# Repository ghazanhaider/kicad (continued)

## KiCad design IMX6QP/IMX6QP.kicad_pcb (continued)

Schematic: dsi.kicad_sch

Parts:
U1: MCIMX6QP5EYM; BGA-624_21x21mm_Layout25x25_P0.8mm

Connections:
CSI_D1M: U1.D1 (CSI_D1M); also elsewhere on the board
CSI_D1P: U1.D2 (CSI_D1P); also elsewhere on the board
CSI_D3P: U1.F1 (CSI_D3P); also elsewhere on the board
HDMI_VPH: U1.K7 (NVCC_MIPI); also elsewhere on the board

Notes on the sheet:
MIPI Display Check standards
MIPI camera RPI uses 15-pin 1mm connector (SFW15R-2STE1LF) with this pinout: 1 GND 2 D0_N 3 D0_P 4 GND 5 D1_N 6 D1_P 7 GND 8 CK_N 9 CK_P 10 GND 11 IO0 - Power enable 12 IO1 - LED indicator 13 SCL 14 SDA 15 3V3 This connector looks like 16-bit parallel/RGB input

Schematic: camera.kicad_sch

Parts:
U1: MCIMX6QP5EYM; BGA-624_21x21mm_Layout25x25_P0.8mm

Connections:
3V3_SW2: U1.N7 (NVCC_CSI); also elsewhere on the board
CSI0_DAT5: U1.P2 (CSI0_DAT5); also elsewhere on the board
CSI0_DATA_EN: U1.P3 (CSI0_DATA_EN); also elsewhere on the board
CSI0_MCLK: U1.P4 (CSI0_MCLK); also elsewhere on the board
CSI0_PIXCLK: U1.P1 (CSI0_PIXCLK); also elsewhere on the board
I2C1_SCL: U1.N5 (CSI0_DAT9); also elsewhere on the board
I2C1_SDA: U1.N6 (CSI0_DAT8); also elsewhere on the board
UART1_RX_DATA: U1.M3 (CSI0_DAT11); also elsewhere on the board
UART1_TX_DATA: U1.M1 (CSI0_DAT10); also elsewhere on the board

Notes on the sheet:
Do not use

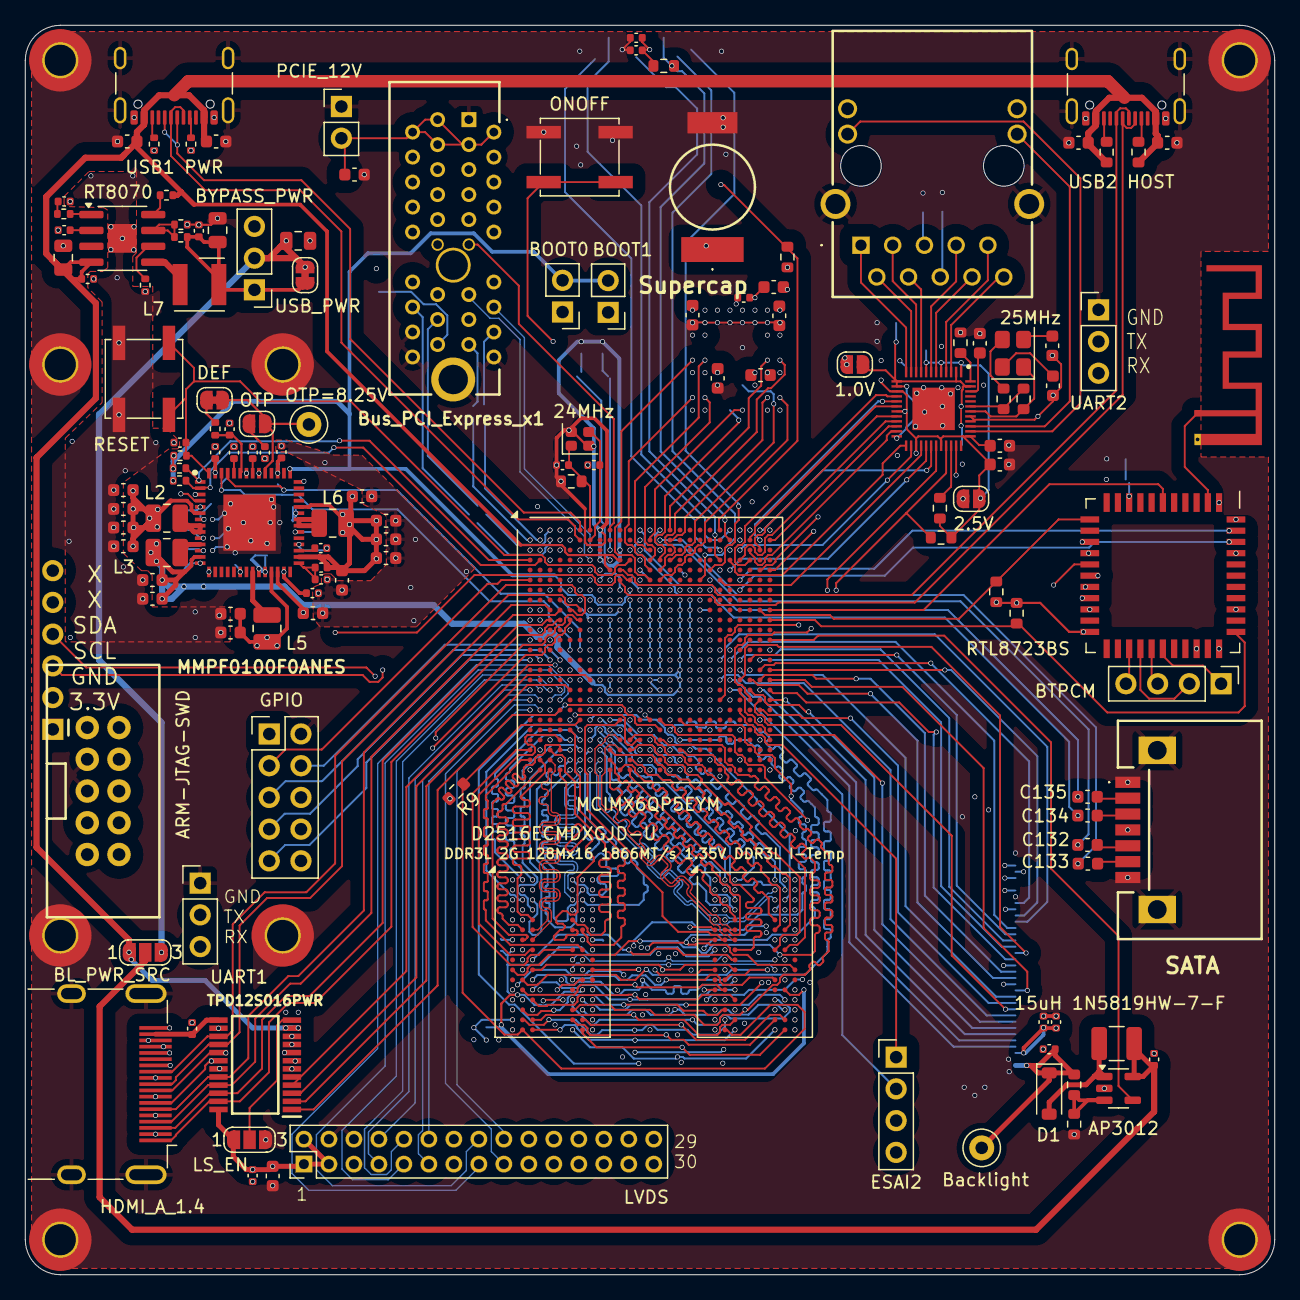
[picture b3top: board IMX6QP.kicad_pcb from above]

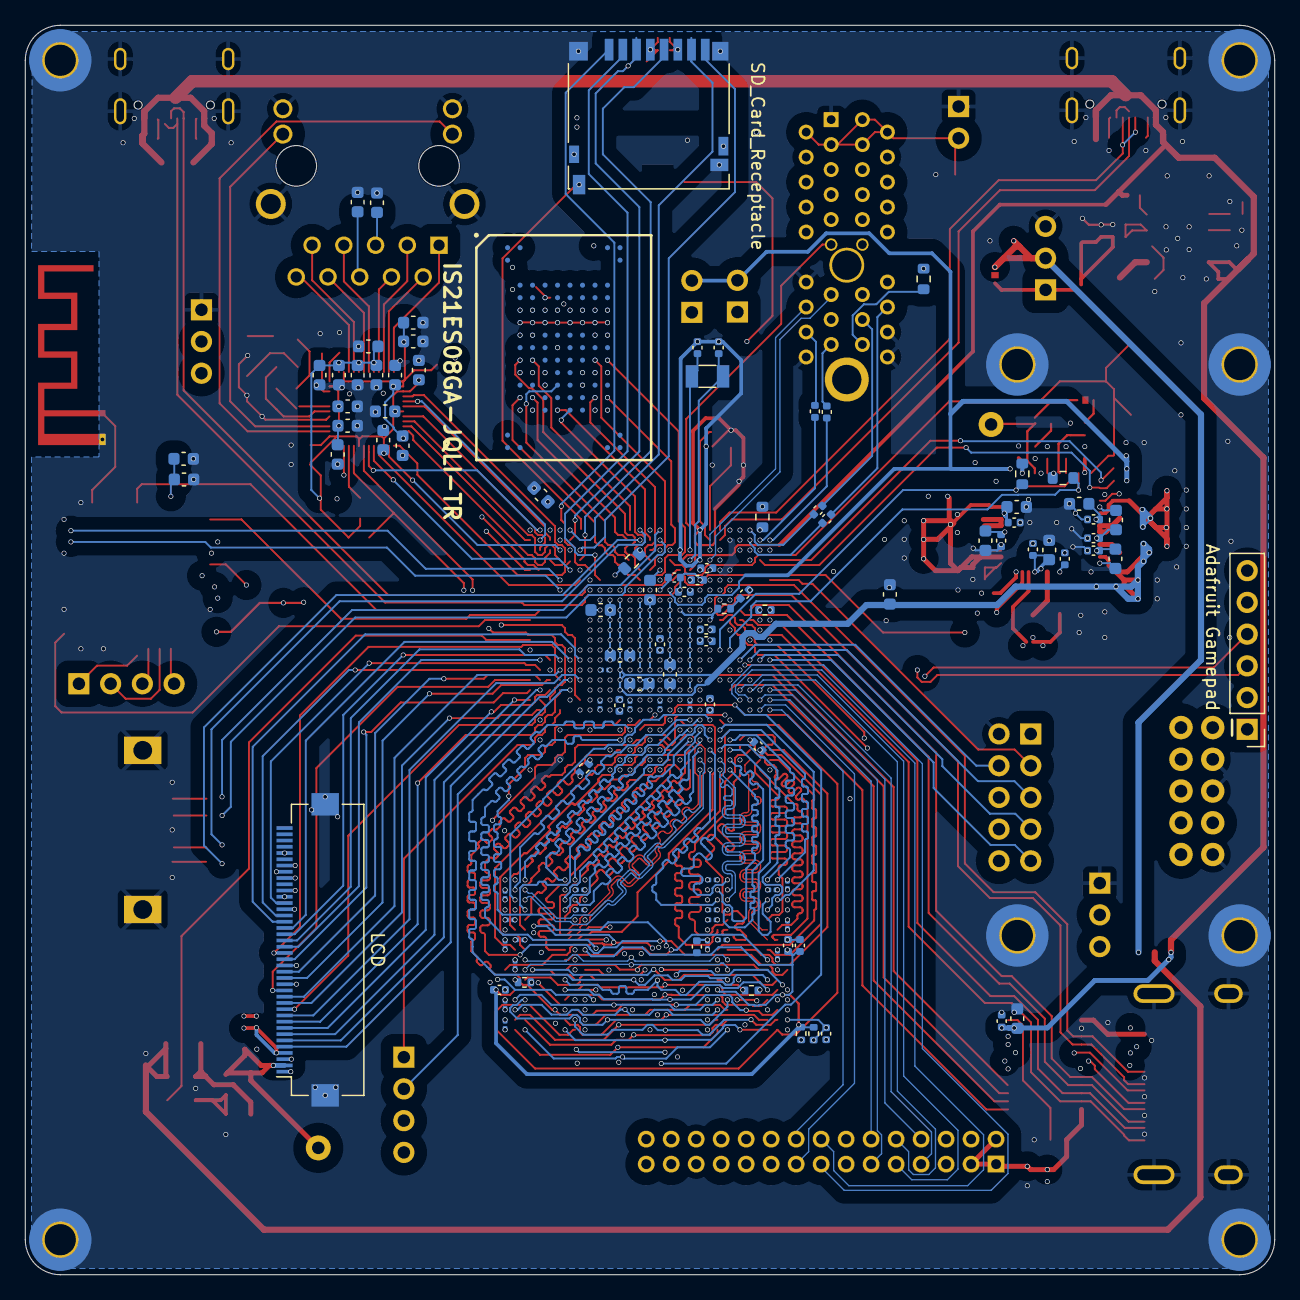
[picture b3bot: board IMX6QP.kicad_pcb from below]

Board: 6 copper layers, 100.0 x 100.0 mm, 248 parts (103 on the bottom side), 314 nets.

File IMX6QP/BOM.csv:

"Reference","Value","Datasheet","Footprint","Qty","DNP"
"AE1","PCB Antenna","~","RF_Antenna:Texas_SWRA117D_2.4GHz_Left","1",""
"BT1","Supercap","RSCSK2243R3D02008U","GhazanCustom:RSCSK2243R3D02008U","1",""
"C1,C2","10pF","~","Capacitor_SMD:C_0402_1005Metric","2",""
"C11,C12,C53,C66,C88,C89","1uF","~","Capacitor_SMD:C_0402_1005Metric","6",""
"C13,C14,C15,C17,C18,C19,C20,C46,C48,C50,C52,C54,C57,C59,C60,C61,C62,C65,C71,C72,C104,C120,C121,C123,C129,C131,C138,C139","0.1uF","~","Capacitor_SMD:C_0402_1005Metric","28",""
"C16","47uF","~","Capacitor_SMD:C_0402_1005Metric","1",""
"C21,C22,C23,C24,C25,C27,C28,C29,C30,C31,C32,C33,C34,C35,C36,C37,C38,C39,C40,C41,C42,C43,C44","0.22uF","~","Capacitor_SMD:C_0201_0603Metric","23",""
"C26","22uF","~","Capacitor_SMD:C_0402_1005Metric","1",""
"C45,C47,C49,C51,C55,C58,C67,C122,C124,C126,C140,C144","4.7uF","~","Capacitor_SMD:C_0603_1608Metric","12",""
"C63,C68,C130,C150,C151,C152,C156","10uF","~","Capacitor_SMD:C_0603_1608Metric","7",""
"C64,C112,C114,C117,C125,C127","2.2uF","~","Capacitor_SMD:C_0603_1608Metric","6",""
"C73,C81,C82,C83,C128","10uF","~","Capacitor_SMD:C_0402_1005Metric","5",""
"C75,C76,C77,C78,C79,C80,C90,C91,C92,C93,C94,C95,C96,C97,C100,C101,C102,C103,C111,C118","22uF","~","Capacitor_SMD:C_0603_1608Metric","20",""
"C84,C87,C106,C107,C110,C136,C137,C141,C142,C143","0.22uF","~","Capacitor_SMD:C_0402_1005Metric","10",""
"C85,C86","22pF","~","Capacitor_SMD:C_0402_1005Metric","2",""
"C105,C109,C119","22uF","~","Capacitor_SMD:C_0805_2012Metric","3",""
"C108","560pF","~","Capacitor_SMD:C_0402_1005Metric","1",""
"C113,C132,C133,C134,C135,C145,C146","10nF","~","Capacitor_SMD:C_0603_1608Metric","7",""
"C147,C148,C149,C153,C154,C155,C157,C158,C159,C160,C161,C162,C163,C164,C165","0.1uF","~","Capacitor_SMD:C_0603_1608Metric","15",""
"D1","1N5819HW-7-F","~","Diode_SMD:D_SOD-123","1",""
"IC1,IC2","D2516ECMDXGJD-U","D2516ECMDXGJD-U","Package_BGA:BGA-96_9.0x13.0mm_Layout2x3x16_P0.8mm","2",""
"IC3","MMPF0100F0ANES","http://www.nxp.com/docs/en/data-sheet/MMPF0100.pdf","GhazanCustom:QFN50P800X800X90-57N-D","1",""
"IC4","VSC8531XMW-02","https://ww1.microchip.com/downloads/en/DeviceDoc/VMDS-10514.pdf","GhazanCustom:QFN40P600X600X90-49N-D","1",""
"IC5","IS21ES08GA-JQLI-TR","https://www.issi.com/WW/pdf/21ES08GA.pdf","GhazanCustom:BGA100C100P10X17_1400X1800X140","1",""
"IC6","TPD12S016PWR","http://www.ti.com/lit/ds/symlink/tpd12s016.pdf","GhazanCustom:SOP65P640X120-24N","1",""
"J1","USB1 PWR","https://www.usb.org/sites/default/files/documents/usb_type-c.zip","Connector_USB:USB_C_Receptacle_GCT_USB4105-xx-A_16P_TopMnt_Horizontal","1",""
"J2","USB2 HOST","https://www.usb.org/sites/default/files/documents/usb_type-c.zip","Connector_USB:USB_C_Receptacle_GCT_USB4105-xx-A_16P_TopMnt_Horizontal","1",""
"J3","Conn_01x40","~","Connector_FFC-FPC:Hirose_FH12-40S-0.5SH_1x40-1MP_P0.50mm_Horizontal","1",""
"J4","GPIO","~","Connector_PinHeader_2.54mm:PinHeader_2x05_P2.54mm_Vertical","1",""
"J5","Adafruit Gamepad","~","Connector_PinHeader_2.54mm:PinHeader_1x06_P2.54mm_Vertical","1",""
"J7","HDMI_A_1.4","https://en.wikipedia.org/wiki/HDMI","Connector_Video:HDMI_A_Molex_208658-1001_Horizontal","1",""
"J8","Bus_PCI_Express_x1","http://www.ritrontek.com/uploadfile/2016/1026/20161026105231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","GhazanCustom:1001878311200TLF","1",""
"J9","SD_Card_Receptacle","http://portal.fciconnect.com/Comergent//fci/drawing/10067847.pdf","Connector_Card:microSD_HC_Hirose_DM3D-SF","1",""
"J10","BOOT0","~","Connector_PinHeader_2.54mm:PinHeader_1x02_P2.54mm_Vertical","1",""
"J11","BOOT1","~","Connector_PinHeader_2.54mm:PinHeader_1x02_P2.54mm_Vertical","1",""
"J12","BYPASS_PWR","~","Connector_PinHeader_2.54mm:PinHeader_1x03_P2.54mm_Vertical","1",""
"J13","ARJM11C7-502-AB-ER2-T","https://abracon.com/Magnetics/ARJM11.pdf","ARJM11C7502ABER2T","1",""
"J14","SATA-A-PL-SMT-K","https://app.adam-tech.com/products/download/data_sheet/20310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","GhazanCustom:SATAAPLSMTK","1",""
"J15","LVDS","~","Connector_PinHeader_2.00mm:PinHeader_2x15_P2.00mm_Vertical","1",""
"J16","UART1","~","Connector_PinHeader_2.54mm:PinHeader_1x03_P2.54mm_Vertical","1",""
"J17","PCIE_12V","~","Connector_PinHeader_2.54mm:PinHeader_1x02_P2.54mm_Vertical","1",""
"J18","UART2","~","Connector_PinHeader_2.54mm:PinHeader_1x03_P2.54mm_Vertical","1",""
"J19","BTPCM","~","Connector_PinHeader_2.54mm:PinHeader_1x04_P2.54mm_Vertical","1",""
"J20","ESAI2","~","Connector_PinHeader_2.54mm:PinHeader_1x04_P2.54mm_Vertical","1",""
"JP2","USB_PWR","~","Jumper:SolderJumper-2_P1.3mm_Bridged_RoundedPad1.0x1.5mm","1",""
"JP3","DEF_PWR","~","Jumper:SolderJumper-2_P1.3mm_Bridged_RoundedPad1.0x1.5mm","1",""
"JP7","LS_EN","~","Jumper:SolderJumper-3_P1.3mm_Open_RoundedPad1.0x1.5mm_NumberLabels","1",""
"L1","15uH NLCV32T-150K-EF","~","Inductor_SMD:L_1210_3225Metric","1",""
"L2,L3,L5,L6","1uH","DFE252012F-1R0M=P2","Inductor_SMD:L_1008_2520Metric","4",""
"L7","2uH","DFE252012P-2R2M=P2","Inductor_SMD_Wurth:L_Wurth_WE-LQSH-4020","1",""
"R1,R2,R8","240R 1%","~","Resistor_SMD:R_0402_1005Metric","3",""
"R3,R25,R36","2k 1%","~","Resistor_SMD:R_0603_1608Metric","3",""
"R4,R5,R9,R29,R31","10k","~","Resistor_SMD:R_0603_1608Metric","5",""
"R6,R7,R37","4.7k","~","Resistor_SMD:R_0603_1608Metric","3",""
"R10,R11","240R","~","Resistor_SMD:R_0402_1005Metric","2",""
"R12","2.2Mohm","~","Resistor_SMD:R_0603_1608Metric","1",""
"R13,R14,R15,R30","100K","~","Resistor_SMD:R_0402_1005Metric","4",""
"R16,R17","330k","~","Resistor_SMD:R_0402_1005Metric","2",""
"R18","33k","~","Resistor_SMD:R_0402_1005Metric","1",""
"R19","75k","~","Resistor_SMD:R_0402_1005Metric","1",""
"R20","24k","~","Resistor_SMD:R_0402_1005Metric","1",""
"R21,R22","5.1k","~","Resistor_SMD:R_0402_1005Metric","2",""
"R23,R24,R32","56k","~","Resistor_SMD:R_0603_1608Metric","3",""
"R26","191R 1%","~","Resistor_SMD:R_0603_1608Metric","1",""
"R27","200R 1%","~","Resistor_SMD:R_0603_1608Metric","1",""
"R28","1.6K 1%","~","Resistor_SMD:R_0402_1005Metric","1",""
"R33","39R 5%","~","Resistor_SMD:R_0603_1608Metric","1",""
"R34","1M 5%","~","Resistor_SMD:R_0603_1608Metric","1",""
"R35","10k 1%","~","Resistor_SMD:R_0603_1608Metric","1",""
"R38","100m","~","Resistor_SMD:R_0402_1005Metric","1",""
"RT1","~","RT8070","Package_SO:HSOP-8-1EP_3.9x4.9mm_P1.27mm_EP2.3x2.3mm","1",""
"SW1","ONOFF","~","Button_Switch_SMD:SW_SPST_EVPBF","1",""
"SW2","RESET","~","Button_Switch_SMD:SW_SPST_EVPBF","1",""
"TP1","Backlight","~","TestPoint:TestPoint_Loop_D1.80mm_Drill1.0mm_Beaded","1",""
"TP2","OTP 8.25V","~","TestPoint:TestPoint_Loop_D1.80mm_Drill1.0mm_Beaded","1",""
"U1","MCIMX6QP5EYM","https://www.nxp.com/docs/en/data-sheet/IMX6DQPCEC.pdf","Package_BGA:BGA-624_21x21mm_Layout25x25_P0.8mm","1",""
"U2","ARM-JTAG-SWD","","GhazanCustom:ARM-JTAG-10-SWD-IDC","1",""
"U6","AP3012","https://www.diodes.com/assets/Datasheets/AP3012.pdf","Package_TO_SOT_SMD:SOT-23-5","1",""
"U7","RTL8723BS(ComboModule)","","GhazanCustom:QFN-44_12x12_Pitch0.9mm","1",""
"Y1","24MHz","XRCGB24M000FBP12R0","Crystal:Crystal_SMD_2016-4Pin_2.0x1.6mm","1",""
"Y3","32kHz","ECS-.327-12.5-34B-TR","Crystal:Crystal_SMD_3215-2Pin_3.2x1.5mm","1",""
"Y4","25MHz","CX3225FB25000B0FZZH1","Crystal:Crystal_SMD_3225-4Pin_3.2x2.5mm","1",""

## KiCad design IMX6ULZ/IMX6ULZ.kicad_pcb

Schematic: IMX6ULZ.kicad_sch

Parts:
U1: MCIMX6Z0DVM09AB; MAPBGA289_NXP

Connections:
1V35: U1.G6 (NVCC_DRAM), U1.H6 (NVCC_DRAM), U1.H9 (VDD_SOC_IN), U1.H10 (VDD_SOC_IN), U1.J6 (NVCC_DRAM), U1.J9 (VDD_SOC_IN), U1.J10 (VDD_SOC_IN), U1.K6 (NVCC_DRAM), U1.K9 (VDD_SOC_IN), U1.K10 (VDD_SOC_IN), U1.L6 (NVCC_DRAM), U1.M6 (NVCC_DRAM); also elsewhere on the board
3V3: U1.C4 (NVCC_SD1), U1.E7 (NVCC_NAND), U1.E13 (NVCC_GPIO3), U1.F4 (NVCC_SD2), U1.F13 (NVCC_KPP), U1.H13 (NVCC_UART), U1.L13 (VDD_HIGH_IN), U1.M13 (VDD_HIGH_IN), U1.N13 (VDD_HIGH_IN), U1.P12 (VDD_SNVS_IN); also elsewhere on the board
BOOT_MODE0: U1.T10 (BOOT_MODE0); also elsewhere on the board
BOOT_MODE1: U1.U10 (BOOT_MODE1); also elsewhere on the board
CCM_PMIC_STBY_REQ: U1.U9 (CCM_PMIC_STBY_REQ); also elsewhere on the board
DRAM_ADDR00: U1.L5 (DRAM_ADDR00); also elsewhere on the board
DRAM_ADDR01: U1.H2 (DRAM_ADDR01); also elsewhere on the board
DRAM_ADDR02: U1.K1 (DRAM_ADDR02); also elsewhere on the board
DRAM_ADDR03: U1.M2 (DRAM_ADDR03); also elsewhere on the board
DRAM_ADDR04: U1.K4 (DRAM_ADDR04); also elsewhere on the board
DRAM_ADDR05: U1.L1 (DRAM_ADDR05); also elsewhere on the board
DRAM_ADDR06: U1.G2 (DRAM_ADDR06); also elsewhere on the board
DRAM_ADDR07: U1.H4 (DRAM_ADDR07); also elsewhere on the board
DRAM_ADDR08: U1.J4 (DRAM_ADDR08); also elsewhere on the board
DRAM_ADDR09: U1.L2 (DRAM_ADDR09); also elsewhere on the board
DRAM_ADDR10: U1.M4 (DRAM_ADDR10); also elsewhere on the board
DRAM_ADDR11: U1.K3 (DRAM_ADDR11); also elsewhere on the board
DRAM_ADDR12: U1.L4 (DRAM_ADDR12); also elsewhere on the board
DRAM_ADDR13: U1.H3 (DRAM_ADDR13); also elsewhere on the board
DRAM_ADDR14: U1.G1 (DRAM_ADDR14); also elsewhere on the board
DRAM_ADDR15: U1.K5 (DRAM_ADDR15); also elsewhere on the board
DRAM_CAS_B: U1.J2 (DRAM_CAS_B); also elsewhere on the board
DRAM_CS0_B: U1.N2 (DRAM_CS0_B); also elsewhere on the board
DRAM_DATA00: U1.T4 (DRAM_DATA00); also elsewhere on the board
DRAM_DATA01: U1.U6 (DRAM_DATA01); also elsewhere on the board
DRAM_DATA02: U1.T6 (DRAM_DATA02); also elsewhere on the board
DRAM_DATA03: U1.U7 (DRAM_DATA03); also elsewhere on the board
DRAM_DATA04: U1.U8 (DRAM_DATA04); also elsewhere on the board
DRAM_DATA05: U1.T8 (DRAM_DATA05); also elsewhere on the board
DRAM_DATA06: U1.T5 (DRAM_DATA06); also elsewhere on the board
DRAM_DATA07: U1.U4 (DRAM_DATA07); also elsewhere on the board
DRAM_DATA08: U1.U2 (DRAM_DATA08); also elsewhere on the board
DRAM_DATA09: U1.U3 (DRAM_DATA09); also elsewhere on the board
DRAM_DATA10: U1.U5 (DRAM_DATA10); also elsewhere on the board
DRAM_DATA11: U1.R4 (DRAM_DATA11); also elsewhere on the board
DRAM_DATA12: U1.P5 (DRAM_DATA12); also elsewhere on the board
DRAM_DATA13: U1.P3 (DRAM_DATA13); also elsewhere on the board
DRAM_DATA14: U1.R2 (DRAM_DATA14); also elsewhere on the board
DRAM_DATA15: U1.R1 (DRAM_DATA15); also elsewhere on the board
DRAM_DQM0: U1.T7 (DRAM_DQM0); also elsewhere on the board
DRAM_DQM1: U1.T3 (DRAM_DQM1); also elsewhere on the board
DRAM_ODT0: U1.N1 (DRAM_ODT0); also elsewhere on the board
DRAM_RAS_B: U1.M5 (DRAM_RAS_B); also elsewhere on the board
DRAM_RESET: U1.G4 (DRAM_RESET); also elsewhere on the board
DRAM_SDBA0: U1.M1 (DRAM_SDBA0); also elsewhere on the board
DRAM_SDBA1: U1.H1 (DRAM_SDBA1); also elsewhere on the board
DRAM_SDBA2: U1.K2 (DRAM_SDBA2); also elsewhere on the board
DRAM_SDCKE0: U1.M3 (DRAM_SDCKE0); also elsewhere on the board
DRAM_SDCLK0_N: U1.P2 (DRAM_SDCLK0_N); also elsewhere on the board
DRAM_SDCLK0_P: U1.P1 (DRAM_SDCLK0_P); also elsewhere on the board
DRAM_SDQS0_N: U1.P7 (DRAM_SDQS0_N); also elsewhere on the board
DRAM_SDQS0_P: U1.P6 (DRAM_SDQS0_P); also elsewhere on the board
DRAM_SDQS1_N: U1.T2 (DRAM_SDQS1_N); also elsewhere on the board
DRAM_SDQS1_P: U1.T1 (DRAM_SDQS1_P); also elsewhere on the board
DRAM_SDWE_B: U1.J1 (DRAM_SDWE_B); also elsewhere on the board
DRAM_VREF: U1.P4 (DRAM_VREF); also elsewhere on the board
DRAM_ZQPAD: U1.N4 (DRAM_ZQPAD); also elsewhere on the board
GND: U1.A1 (VSS), U1.A17 (VSS), U1.C3 (VSS), U1.C7 (VSS), U1.C11 (VSS), U1.C15 (VSS), U1.E8 (VSS), U1.E11 (VSS), U1.F6 (VSS), U1.F7 (VSS), U1.F8 (VSS), U1.F9 (VSS), U1.F10 (VSS), U1.F11 (VSS), U1.F12 (VSS), U1.G3 (VSS), U1.G5 (VSS), U1.G7 (VSS), U1.G12 (VSS), U1.G15 (VSS), U1.H7 (VSS), U1.H12 (VSS), U1.J5 (VSS), U1.J7 (VSS), U1.J12 (VSS), U1.K7 (VSS), U1.K12 (VSS), U1.L3 (VSS), U1.L7 (VSS), U1.L12 (VSS), U1.M7 (VSS), U1.M8 (VSS), U1.M9 (VSS), U1.M10 (VSS), U1.M11 (VSS), U1.M12 (NGND_KEL0), U1.N3 (VSS), U1.N5 (VSS), U1.N7 (TEST_MODE), U1.P15 (JJTAG_MOD), U1.R3 (VSS), U1.R5 (VSS), U1.R7 (VSS), U1.R11 (VSS), U1.R16 (VSS), U1.R17 (VSS), U1.T11 (RTC_XTALI), U1.T14 (VSS), U1.U1 (VSS), U1.U14 (VSS), U1.U17 (VSS); also elsewhere on the board
GPIO1_IO09: U1.M15 (GPIO1_IO09); also elsewhere on the board
GPIO3_IO04: U1.E9 (GPIO3_IO04); also elsewhere on the board
GPIO3_IO06: U1.A9 (GPIO3_IO06); also elsewhere on the board
GPIO3_IO14: U1.A11 (GPIO3_IO14); also elsewhere on the board
GPIO3_IO16: U1.D12 (GPIO3_IO16); also elsewhere on the board
GPIO3_IO17: U1.C12 (GPIO3_IO17); also elsewhere on the board
GPIO3_IO18: U1.B12 (GPIO3_IO18); also elsewhere on the board
GPIO3_IO19: U1.A12 (GPIO3_IO19); also elsewhere on the board
GPIO3_IO20: U1.D13 (GPIO3_IO20); also elsewhere on the board
GPIO3_IO21: U1.C13 (GPIO3_IO21); also elsewhere on the board
GPIO3_IO22: U1.B13 (GPIO3_IO22); also elsewhere on the board
GPIO3_IO23: U1.A13 (GPIO3_IO23); also elsewhere on the board
GPIO3_IO24: U1.D14 (GPIO3_IO24); also elsewhere on the board
GPIO3_IO25: U1.C14 (GPIO3_IO25); also elsewhere on the board
GPIO3_IO26: U1.B14 (GPIO3_IO26); also elsewhere on the board
GPIO3_IO27: U1.A14 (GPIO3_IO27); also elsewhere on the board
JTAG_TCK: U1.M14 (JTAG_TCK); also elsewhere on the board
JTAG_TDI: U1.N16 (JTAG_TDI); also elsewhere on the board
JTAG_TDO: U1.N15 (JTAG_TDO); also elsewhere on the board
JTAG_TMS: U1.P14 (JTAG_TMS); also elsewhere on the board
JTAG_TRST_B: U1.N14 (JTAG_TRST_B); also elsewhere on the board
KPP_COL0: U1.E17 (KPP_COL0); also elsewhere on the board
KPP_COL1: U1.E15 (KPP_COL1); also elsewhere on the board
KPP_COL2: U1.F15 (KPP_COL2); also elsewhere on the board
KPP_COL3: U1.D15 (KPP_COL3); also elsewhere on the board
KPP_COL4: U1.C16 (KPP_COL4); also elsewhere on the board
KPP_COL5: U1.A15 (KPP_COL5); also elsewhere on the board
KPP_COL6: U1.B15 (KPP_COL6); also elsewhere on the board
KPP_ROW0: U1.F16 (KPP_ROW0); also elsewhere on the board
KPP_ROW1: U1.E16 (KPP_ROW1); also elsewhere on the board
KPP_ROW2: U1.E14 (KPP_ROW2); also elsewhere on the board
KPP_ROW3: U1.F14 (KPP_ROW3); also elsewhere on the board
KPP_ROW4: U1.C17 (KPP_ROW4); also elsewhere on the board
KPP_ROW5: U1.B17 (KPP_ROW5); also elsewhere on the board
KPP_ROW6: U1.A16 (KPP_ROW6); also elsewhere on the board
MQS_LEFT: U1.L15 (GPIO1_IO01); also elsewhere on the board
MQS_RIGHT: U1.K13 (GPIO1_IO00); also elsewhere on the board
NAND_CE0_B: U1.C5 (NAND_CE0_B); also elsewhere on the board
NAND_CE1_B: U1.B5 (NAND_CE1_B); also elsewhere on the board
NAND_CLE: U1.A4 (NAND_CLE); also elsewhere on the board
NAND_DATA00: U1.D7 (NAND_DATA00); also elsewhere on the board
NAND_DATA01: U1.B7 (NAND_DATA01); also elsewhere on the board
NAND_DATA02: U1.A7 (NAND_DATA02); also elsewhere on the board
NAND_DATA03: U1.D6 (NAND_DATA03); also elsewhere on the board
NAND_DQS: U1.E6 (NAND_DQS); also elsewhere on the board
NAND_READY_B: U1.A3 (NAND_READY_B); also elsewhere on the board
NAND_RE_B: U1.D8 (NAND_RE_B); also elsewhere on the board
NAND_WE_B: U1.C8 (NAND_WE_B); also elsewhere on the board
NAND_WP_B: U1.D5 (NAND_WP_B); also elsewhere on the board
NVCC_DRAM_2P5: U1.N6 (NVCC_DRAM_2P5), U1.R14 (VDD_HIGH_CAP), U1.R15 (VDD_HIGH_CAP2); also elsewhere on the board
NVCC_PLL: U1.P13 (NVCC_PLL); also elsewhere on the board
ONOFF: U1.R8 (ONOFF); also elsewhere on the board
POR_B: U1.P8 (POR_B); also elsewhere on the board
SD1_CLK: U1.C1 (SD1_CLK); also elsewhere on the board
SD1_CMD: U1.C2 (SD1_CMD); also elsewhere on the board
SD1_DATA0: U1.B3 (SD1_DATA0); also elsewhere on the board
SD1_DATA1: U1.B2 (SD1_DATA1); also elsewhere on the board
SD1_DATA2: U1.B1 (SD1_DATA2); also elsewhere on the board
SD1_DATA3: U1.A2 (SD1_DATA3); also elsewhere on the board
SD2_CLK: U1.F2 (SD2_CLK); also elsewhere on the board
SD2_CMD: U1.F3 (SD2_CMD); also elsewhere on the board
SD2_DATA0: U1.E4 (SD2_DATA0); also elsewhere on the board
SD2_DATA1: U1.E3 (SD2_DATA1); also elsewhere on the board
SD2_DATA2: U1.E2 (SD2_DATA2); also elsewhere on the board
SD2_DATA3: U1.E1 (SD2_DATA3); also elsewhere on the board
SNVS_PMIC_ON_REQ: U1.T9 (SNVS_PMIC_ON_REQ); also elsewhere on the board
UART1_CTS_B: U1.K15 (UART1_CTS_B); also elsewhere on the board
UART1_RTS_B: U1.J14 (UART1_RTS_B); also elsewhere on the board
UART1_RX_DATA: U1.K16 (UART1_RX_DATA); also elsewhere on the board
UART1_TX_DATA: U1.K14 (UART1_TX_DATA); also elsewhere on the board
UART2_RX_DATA: U1.J16 (UART2_RX_DATA); also elsewhere on the board
UART2_TX_DATA: U1.J17 (UART2_TX_DATA); also elsewhere on the board
UART3_CTS_B: U1.H15 (UART3_CTS_B); also elsewhere on the board
UART3_RTS_B: U1.G14 (UART3_RTS_B); also elsewhere on the board
UART3_RX_DATA: U1.H16 (UART3_RX_DATA); also elsewhere on the board
UART3_TX_DATA: U1.H17 (UART3_TX_DATA); also elsewhere on the board
USB_OTG1_DN: U1.T15 (USB_OTG1_DN); also elsewhere on the board
USB_OTG1_DP: U1.U15 (USB_OTG1_DP); also elsewhere on the board
USB_OTG1_VBUS: U1.T12 (USB_OTG1_VBUS), U1.U12 (USB_OTG2_VBUS); also elsewhere on the board
USB_OTG2_DN: U1.T13 (USB_OTG2_DN); also elsewhere on the board
USB_OTG2_DP: U1.U13 (USB_OTG2_DP); also elsewhere on the board
VDD_ARM_CAP: U1.G9 (VDD_ARM_CAP), U1.G10 (VDD_ARM_CAP), U1.G11 (VDD_ARM_CAP), U1.H11 (VDD_ARM_CAP); also elsewhere on the board
VDD_SNVS_CAP: U1.N12 (VDD_SNVS_CAP); also elsewhere on the board
VDD_SOC_CAP: U1.G8 (VDD_SOC_CAP), U1.H8 (VDD_SOC_CAP), U1.J8 (VDD_SOC_CAP), U1.J11 (VDD_SOC_CAP), U1.K8 (VDD_SOC_CAP), U1.K11 (VDD_SOC_CAP), U1.L8 (VDD_SOC_CAP), U1.L9 (VDD_SOC_CAP), U1.L10 (VDD_SOC_CAP), U1.L11 (VDD_SOC_CAP); also elsewhere on the board
VDD_USB_CAP: U1.R12 (VDD_USB_CAP); also elsewhere on the board
XTALI: U1.T16 (XTALI); also elsewhere on the board
XTALO: U1.T17 (XTALO); also elsewhere on the board

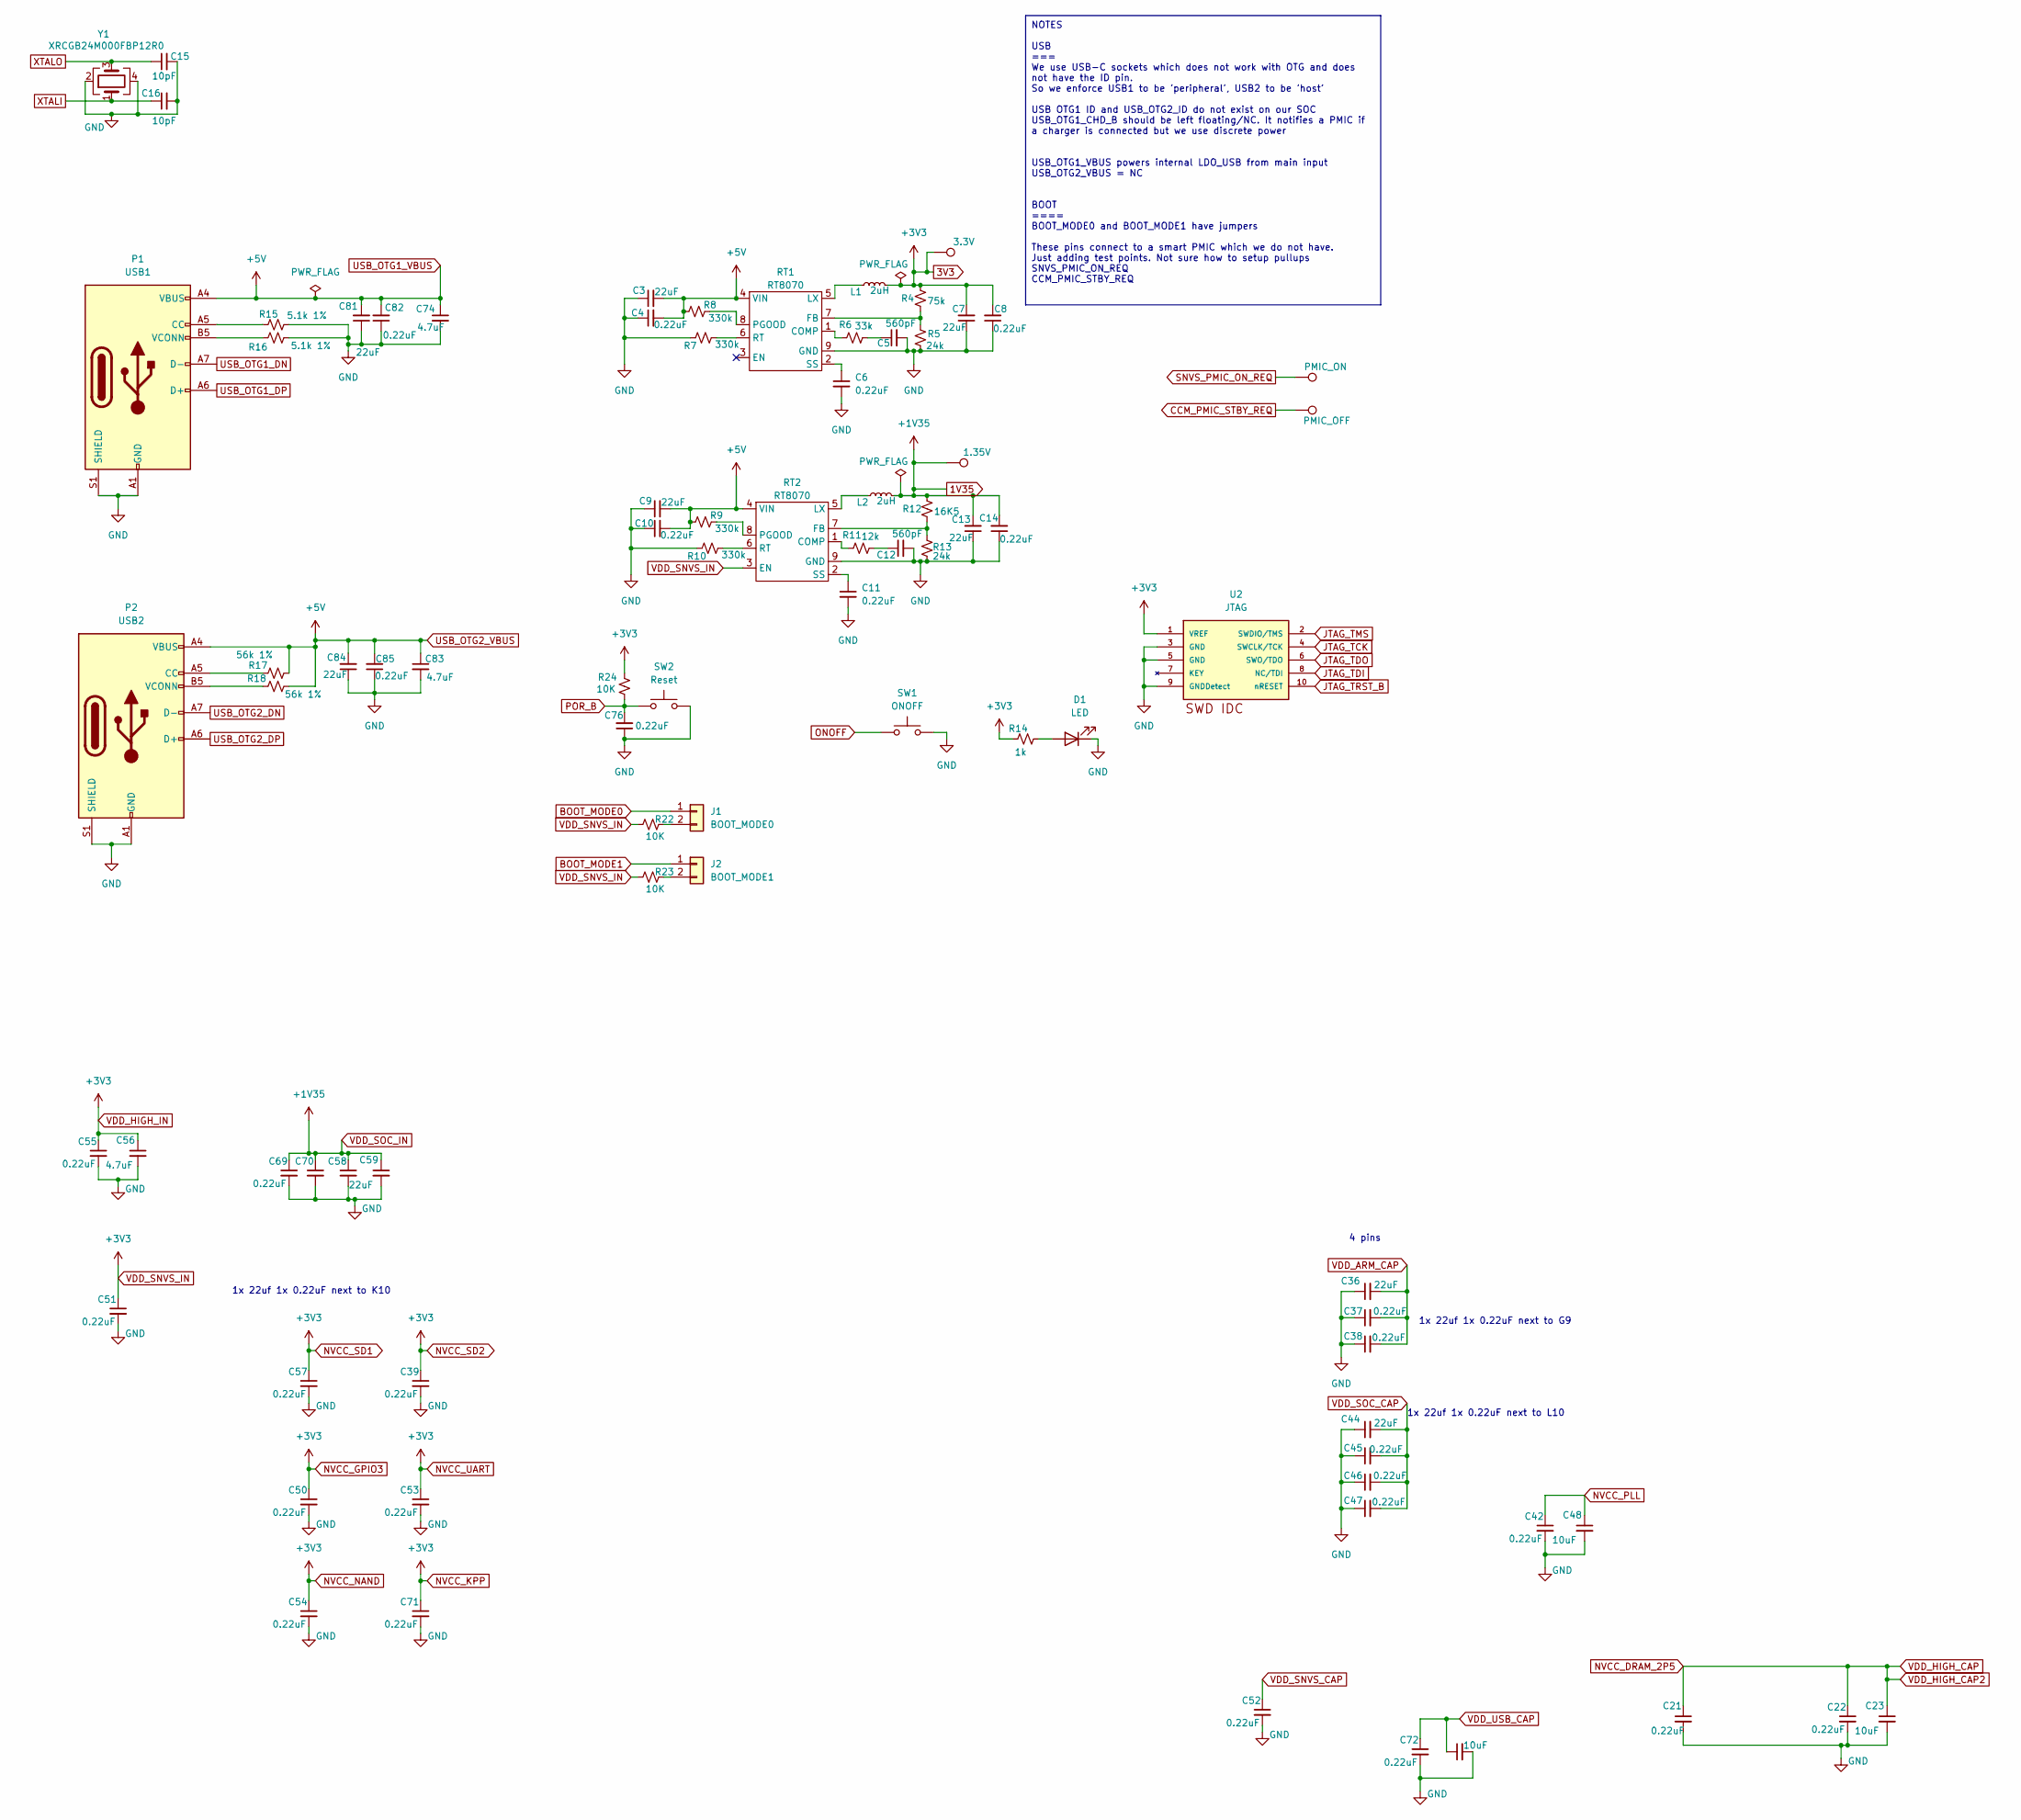
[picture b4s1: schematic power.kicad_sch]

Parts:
C3, C7, C9, C13, C36: 22uF; C_0805_2012Metric
C4, C6, C8, C10, C11, C14, C76, C82, C85: 0.22uF; C_0402_1005Metric
C5, C12: 560pF; C_0402_1005Metric
C15, C16: 10pF; C_0402_1005Metric
C17, C23, C48: 10uF; C_0402_1005Metric
C21, C22, C37, C38, C39, C42, C45, C46, C47, C50, C51, C52, C53, C54, C55, C57, C58, C69, C71, C72: 0.22uF; C_0201_0603Metric
C44, C59, C81, C84: 22uF; C_0402_1005Metric
C56, C70, C74, C83: 4.7uF; C_0402_1005Metric
D1: LED; LED_0805_2012Metric
J1: BOOT_MODE0; PinHeader_1x02_P2.54mm_Vertical
J2: BOOT_MODE1; PinHeader_1x02_P2.54mm_Vertical
L1, L2: 2uH; L_Wurth_WE-LQSH-4020
P1: USB1; USB_C_Receptacle_GCT_USB4105-xx-A_16P_TopMnt_Horizontal
P2: USB2; USB_C_Receptacle_GCT_USB4105-xx-A_16P_TopMnt_Horizontal
R4: 75k; R_0402_1005Metric
R5, R13: 24k; R_0402_1005Metric
R6: 33k; R_0402_1005Metric
R7, R8, R9, R10: 330k; R_0402_1005Metric
R11: 12k; R_0402_1005Metric
R12: 16K5; R_0402_1005Metric
R14: 1k; R_0402_1005Metric
R15, R16: 5.1k 1%; R_0402_1005Metric
R17, R18: 56k 1%; R_0402_1005Metric
R22, R23, R24: 10K; R_0402_1005Metric
RT1, RT2: RT8070; HSOP-8-1EP_3.9x4.9mm_P1.27mm_EP2.3x2.3mm
SW1: ONOFF; SW_SPST_PTS645
SW2: Reset; SW_SPST_PTS645
TP3: PMIC_ON; TestPoint_Pad_D1.0mm
TP4: PMIC_OFF; TestPoint_Pad_D1.0mm
TP6: 3.3V; TestPoint_THTPad_D1.5mm_Drill0.7mm
TP7: 1.35V; TestPoint_THTPad_D1.5mm_Drill0.7mm
U2: JTAG; PinHeader_2x10_P2.54mm_Vertical
Y1: XRCGB24M000FBP12R0; Crystal_SMD_2016-4Pin_2.0x1.6mm

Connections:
1V35: C13.2, C14.2, C58.1, C59.1, C69.1, C70.1, L2.2, R12.1, TP7.1; also elsewhere on the board
3V3: C7.2, C8.2, C39.1, C50.1, C51.1, C53.1, C54.1, C55.1, C56.1, C57.1, C71.1, L1.2, R4.1, R14.1, R22.1, R23.1, R24.2, RT2.3 (EN), TP6.1, U2.1 (VREF); also elsewhere on the board
BOOT_MODE0: J1.1; also elsewhere on the board
BOOT_MODE1: J2.1; also elsewhere on the board
CCM_PMIC_STBY_REQ: TP4.1; also elsewhere on the board
GND: C3.1, C4.1, C5.2, C6.2, C7.1, C8.1, C9.1, C10.1, C11.2, C12.2, C13.1, C14.1, C15.2, C16.2, C17.2, C21.2, C22.2, C23.2, C36.1, C37.1, C38.1, C39.2, C42.2, C44.1, C45.1, C46.1, C47.1, C48.2, C50.2, C51.2, C52.2, C53.2, C54.2, C55.2, C56.2, C57.2, C58.2, C59.2, C69.2, C70.2, C71.2, C72.2, C74.2, C76.1, C81.1, C82.1, C83.2, C84.1, C85.1, D1.1 (K), P1.A1 (GND), P1.A12 (GND), P1.B1 (GND), P1.B12 (GND), P1.S1 (SHIELD), P2.A1 (GND), P2.A12 (GND), P2.B1 (GND), P2.B12 (GND), P2.S1 (SHIELD), R5.2, R7.1, R10.1, R13.2, R15.2, R16.2, RT1.9 (GND), RT2.9 (GND), SW1.2, SW2.2, U2.3 (GND), U2.5 (GND), U2.9 (GNDDetect), Y1.2, Y1.4; also elsewhere on the board
JTAG_TCK: U2.4 (SWCLK/TCK); also elsewhere on the board
JTAG_TDI: U2.8 (NC/TDI); also elsewhere on the board
JTAG_TDO: U2.6 (SWO/TDO); also elsewhere on the board
JTAG_TMS: U2.2 (SWDIO/TMS); also elsewhere on the board
JTAG_TRST_B: U2.10 (nRESET); also elsewhere on the board
NVCC_DRAM_2P5: C21.1, C22.1, C23.1; also elsewhere on the board
NVCC_PLL: C42.1, C48.1; also elsewhere on the board
unnamed: C5.1, R6.2
unnamed: C12.1, R11.2
unnamed: D1.2 (A), R14.2
unnamed: J1.2, R22.2
unnamed: J2.2, R23.2
unnamed: P1.A5 (CC), R15.1
unnamed: P1.B5 (VCONN), R16.1
unnamed: P2.A5 (CC), R17.1
unnamed: P2.B5 (VCONN), R18.1
unnamed: R6.1, RT1.1 (COMP)
unnamed: R4.2, R5.1, RT1.7 (FB)
unnamed: L1.1, RT1.5 (LX)
unnamed: R8.2, RT1.8 (PGOOD)
unnamed: R7.2, RT1.6 (RT)
unnamed: C6.1, RT1.2 (SS)
unnamed: R11.1, RT2.1 (COMP)
unnamed: R12.2, R13.1, RT2.7 (FB)
unnamed: L2.1, RT2.5 (LX)
unnamed: R9.2, RT2.8 (PGOOD)
unnamed: R10.2, RT2.6 (RT)
unnamed: C11.1, RT2.2 (SS)
ONOFF: SW1.1; also elsewhere on the board
POR_B: C76.2, R24.1, SW2.1; also elsewhere on the board
SNVS_PMIC_ON_REQ: TP3.1; also elsewhere on the board
USB_OTG1_DN: P1.A7 (D-); also elsewhere on the board
USB_OTG1_DP: P1.A6 (D+); also elsewhere on the board
USB_OTG1_VBUS: C3.2, C4.2, C9.2, C10.2, C74.1, C81.2, C82.2, C83.1, C84.2, C85.2, P1.A4 (VBUS), P1.A9 (VBUS), P1.B4 (VBUS), P1.B9 (VBUS), P2.A4 (VBUS), P2.A9 (VBUS), P2.B4 (VBUS), P2.B9 (VBUS), R8.1, R9.1, R17.2, R18.2, RT1.4 (VIN), RT2.4 (VIN); also elsewhere on the board
USB_OTG2_DN: P2.A7 (D-); also elsewhere on the board
USB_OTG2_DP: P2.A6 (D+); also elsewhere on the board
VDD_ARM_CAP: C36.2, C37.2, C38.2; also elsewhere on the board
VDD_SNVS_CAP: C52.1; also elsewhere on the board
VDD_SOC_CAP: C44.2, C45.2, C46.2, C47.2; also elsewhere on the board
VDD_USB_CAP: C17.1, C72.1; also elsewhere on the board
XTALI: C16.1, Y1.1; also elsewhere on the board
XTALO: C15.1, Y1.3; also elsewhere on the board

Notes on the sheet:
NOTES USB === We use USB-C sockets which does not work with OTG and does not have the ID pin. So we enforce USB1 to be 'peripheral', USB2 to be 'host' USB OTG1 ID and USB_OTG2_ID do not exist on our SOC USB_OTG1_CHD_B should be left floating/NC. It notifies a PMIC if a charger is connected but we u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
1x 22uf 1x 0.22uF next to L10
1x 22uf 1x 0.22uF next to K10
4 pins
1x 22uf 1x 0.22uF next to G9
